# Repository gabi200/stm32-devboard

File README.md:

# stm32-devboard
Simple, cost-effective **STM32** development board with onboard voltage regulator and I2C EEPROM. The provided files include both the electrical schematic and the PCB layout. The design has been fabricated at JLCPCB and validated in real-life operation. 

**Caution: Please note that the component assembly was performed manually, so the design does not take into consideration automated assembly.**
## Board specifications

 - STM32L4-family microcontroller
 - AMS1117 voltage regulator
 - M24256E-F 256-Kbit I2C EEPROM
 - GPIO and Debug/Programming headers
 - 3.3V I/O voltage
 - Maximum recommended VIN voltage: 12V

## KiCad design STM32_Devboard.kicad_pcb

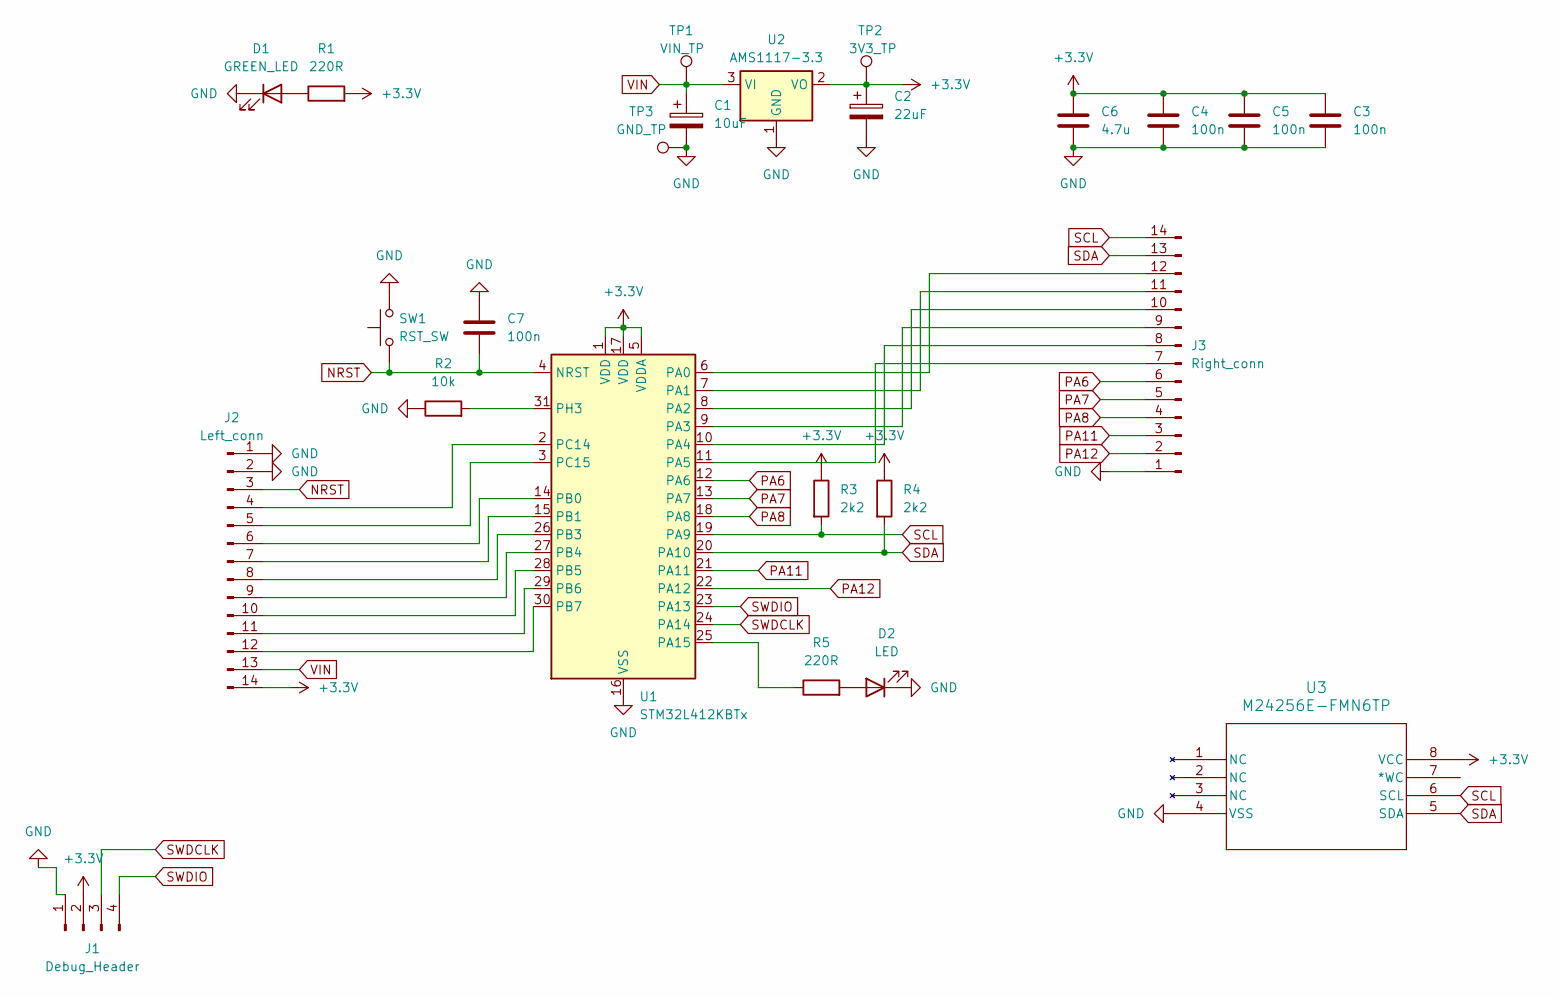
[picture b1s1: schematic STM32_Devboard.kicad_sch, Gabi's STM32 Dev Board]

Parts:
C1: 10uF; CP_EIA-3528-21_Kemet-B_Pad1.50x2.35mm_HandSolder
C2: 22uF; CP_EIA-6032-28_Kemet-C_Pad2.25x2.35mm_HandSolder
C3, C4, C5, C7: 100n; C_1206_3216Metric_Pad1.33x1.80mm_HandSolder
C6: 4.7u; C_1206_3216Metric_Pad1.33x1.80mm_HandSolder
D1: GREEN_LED; LED_Yuji_5730
D2: LED; LED_Yuji_5730
J1: Debug_Header; PinHeader_1x04_P2.54mm_Vertical
J2: Left_conn; PinHeader_1x14_P2.54mm_Vertical
J3: Right_conn; PinHeader_1x14_P2.54mm_Vertical
R1, R5: 220R; R_1206_3216Metric_Pad1.30x1.75mm_HandSolder
R2: 10k; R_1206_3216Metric_Pad1.30x1.75mm_HandSolder
R3, R4: 2k2; R_1206_3216Metric_Pad1.30x1.75mm_HandSolder
SW1: RST_SW; SW_PUSH_6mm_H9.5mm
TP1: VIN_TP; TestPoint_Pad_D1.5mm
TP2: 3V3_TP; TestPoint_Pad_D1.5mm
TP3: GND_TP; TestPoint_Pad_D1.5mm
U1: STM32L412KBTx; LQFP-32_7x7mm_P0.8mm
U2: AMS1117-3.3; SOT-223-3_TabPin2
U3: M24256E-FMN6TP; SO8N_4X5X1P27_STM

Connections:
+3.3V: C2.1, C3.1, C4.1, C5.1, C6.1, J1.2, J2.14, R1.2, R3.1, R4.1, TP2.1, U1.1 (VDD), U1.5 (VDDA), U1.17 (VDD), U2.2 (VO), U3.8 (VCC)
GND: C1.2, C2.2, C3.2, C4.2, C5.2, C6.2, C7.1, D1.1 (K), D2.1 (K), J1.1, J2.1, J2.2, J3.1, R2.1, SW1.2, TP3.1, U1.16 (VSS), U1.32 (VSS), U2.1 (GND), U3.4 (VSS)
NRST: C7.2, J2.3, SW1.1, U1.4 (NRST)
unnamed: D1.2 (A), R1.1
unnamed: D2.2 (A), R5.2
unnamed: J2.4, U1.2 (PC14)
unnamed: J2.5, U1.3 (PC15)
unnamed: J2.6, U1.14 (PB0)
unnamed: J2.7, U1.15 (PB1)
unnamed: J2.8, U1.26 (PB3)
unnamed: J2.9, U1.27 (PB4)
unnamed: J2.10, U1.28 (PB5)
unnamed: J2.11, U1.29 (PB6)
unnamed: J2.12, U1.30 (PB7)
unnamed: J3.7, U1.11 (PA5)
unnamed: J3.8, U1.10 (PA4)
unnamed: J3.9, U1.9 (PA3)
unnamed: J3.10, U1.8 (PA2)
unnamed: J3.11, U1.7 (PA1)
unnamed: J3.12, U1.6 (PA0)
unnamed: R5.1, U1.25 (PA15)
unnamed: R2.2, U1.31 (PH3)
PA6: J3.6, U1.12 (PA6)
PA7: J3.5, U1.13 (PA7)
PA8: J3.4, U1.18 (PA8)
PA11: J3.3, U1.21 (PA11)
PA12: J3.2, U1.22 (PA12)
SCL: J3.14, R3.2, U1.19 (PA9), U3.6 (SCL)
SDA: J3.13, R4.2, U1.20 (PA10), U3.5 (SDA)
SWDCLK: J1.3, U1.24 (PA14)
SWDIO: J1.4, U1.23 (PA13)
VIN: C1.1, J2.13, TP1.1, U2.3 (VI)

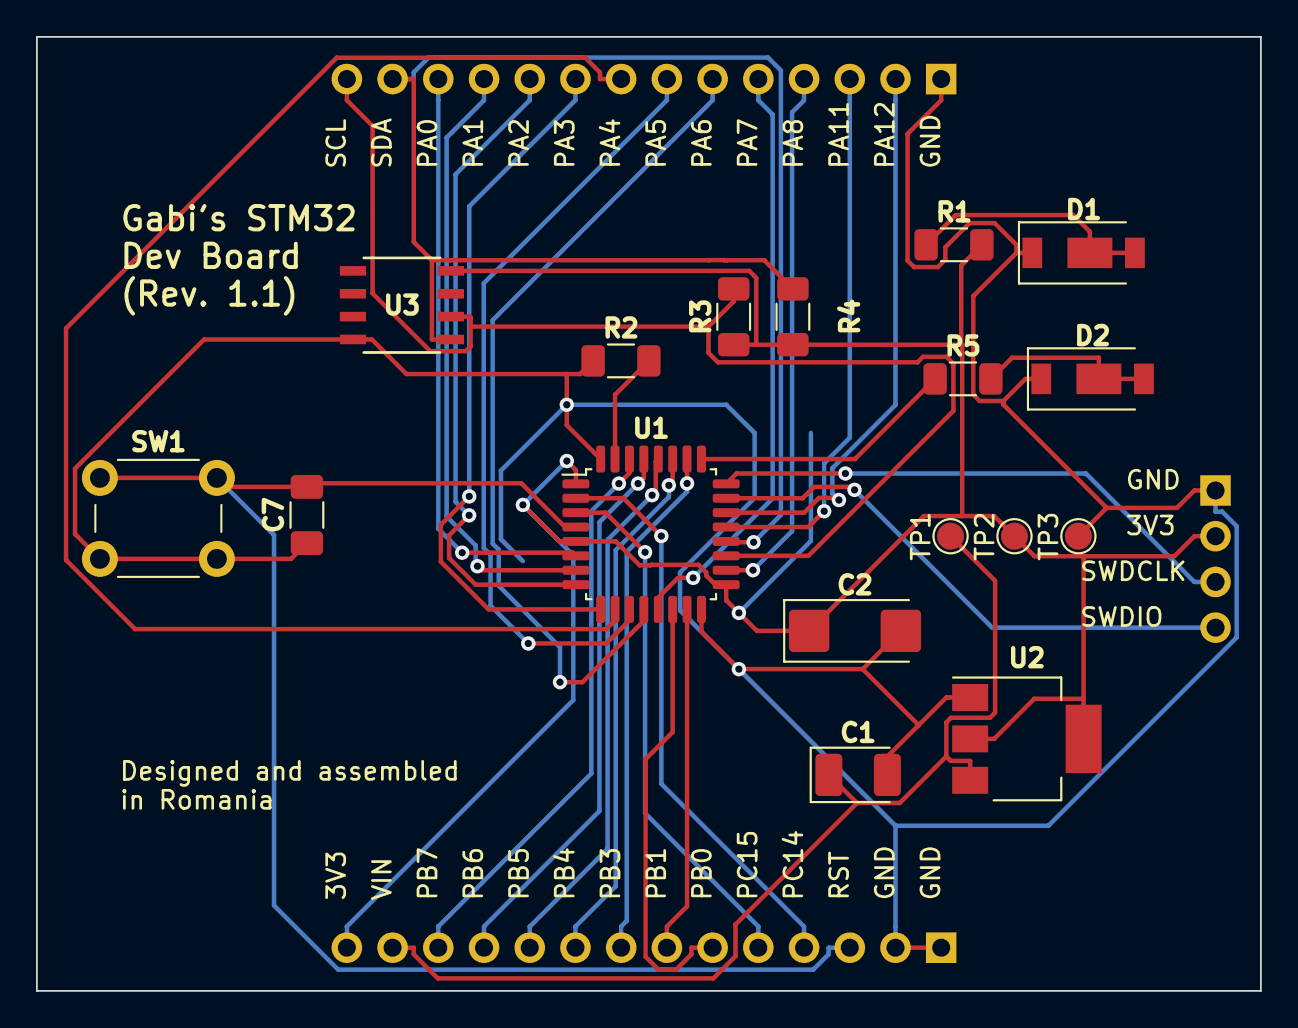
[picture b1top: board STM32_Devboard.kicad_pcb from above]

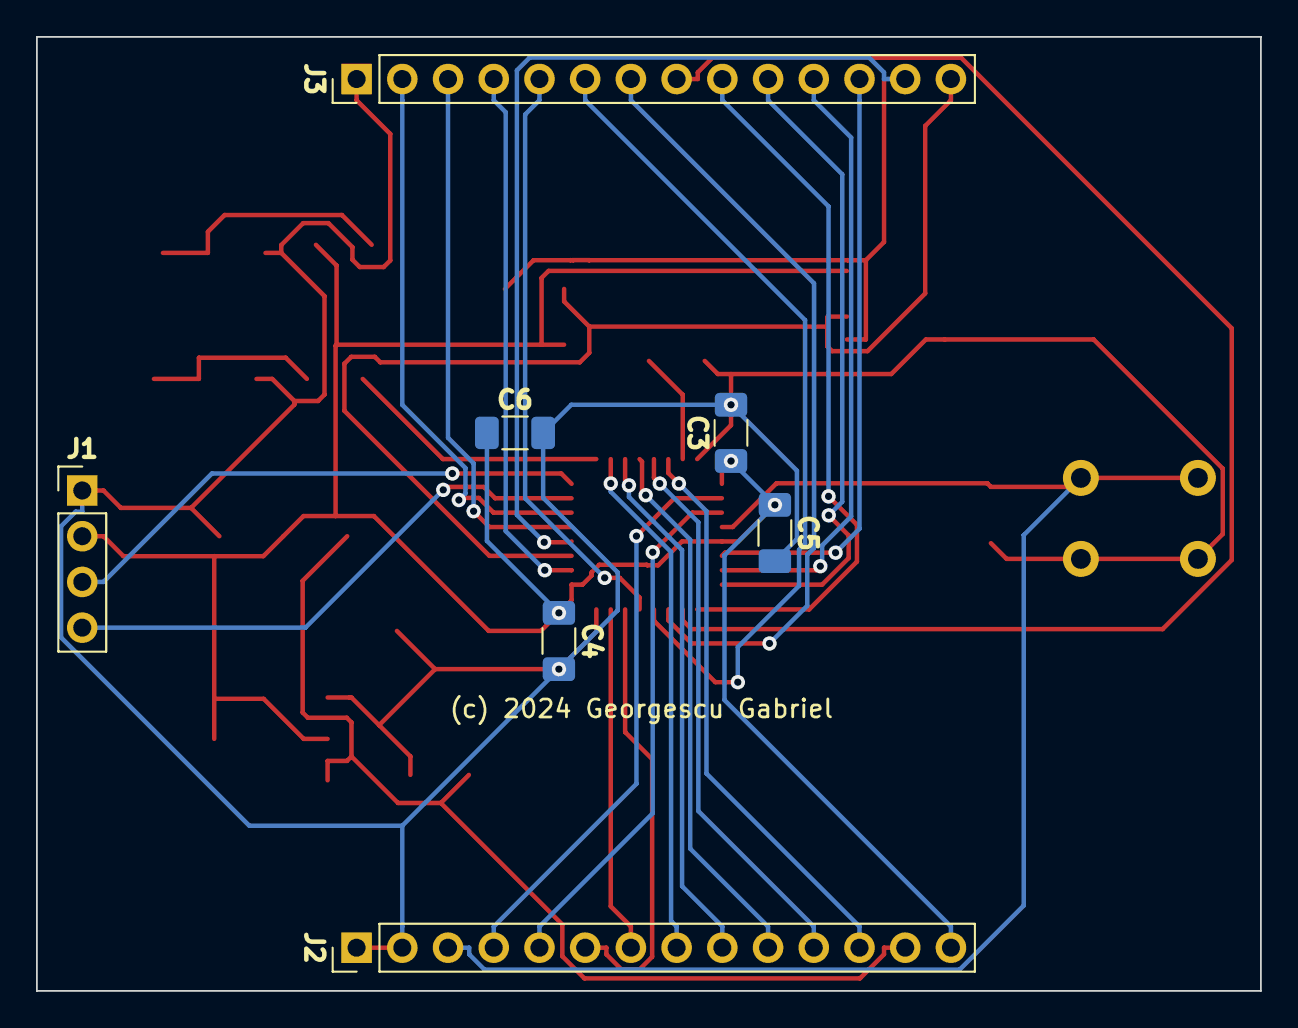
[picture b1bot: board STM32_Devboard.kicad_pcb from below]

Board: 2 copper layers, 68.0 x 53.0 mm, 24 parts (7 on the bottom side), 32 nets.

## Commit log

2025-12-01 Added board files
2025-12-01 updated README
    Added a caution note regarding manual assembly of components.

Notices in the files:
STM32_Devboard.kicad_pcb:
(c) 2024 Georgescu Gabriel
